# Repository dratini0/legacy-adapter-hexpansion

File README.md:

# "Legacy" connector adapter

Adapts the tildagon to various other interfaces.

* Any of the various I2C over JST SH standards (Compatible with Adafruit Stemma QT/Sparkfun Qwiic)
* [Shitty Add-On](https://hackaday.io/project/52950-shitty-add-ons/log/159806-introducing-the-shitty-add-on-v169bis-standard/)
* The expansion connector from TiDAL (hence the name)

## Acknowledgements

Uses the [hexpansion template from EMF](https://github.com/emfcamp/badge-2024-hardware/tree/main/hexpansion).
The footprint for the TiDAL expansion connector is also (unsurprisingly) [borrowed from EMF](https://github.com/emfcamp/TiDAL-Hardware/blob/main/tilda6/tilda6.pretty/XUNPU_FPC-05F-8PH20.kicad_mod).

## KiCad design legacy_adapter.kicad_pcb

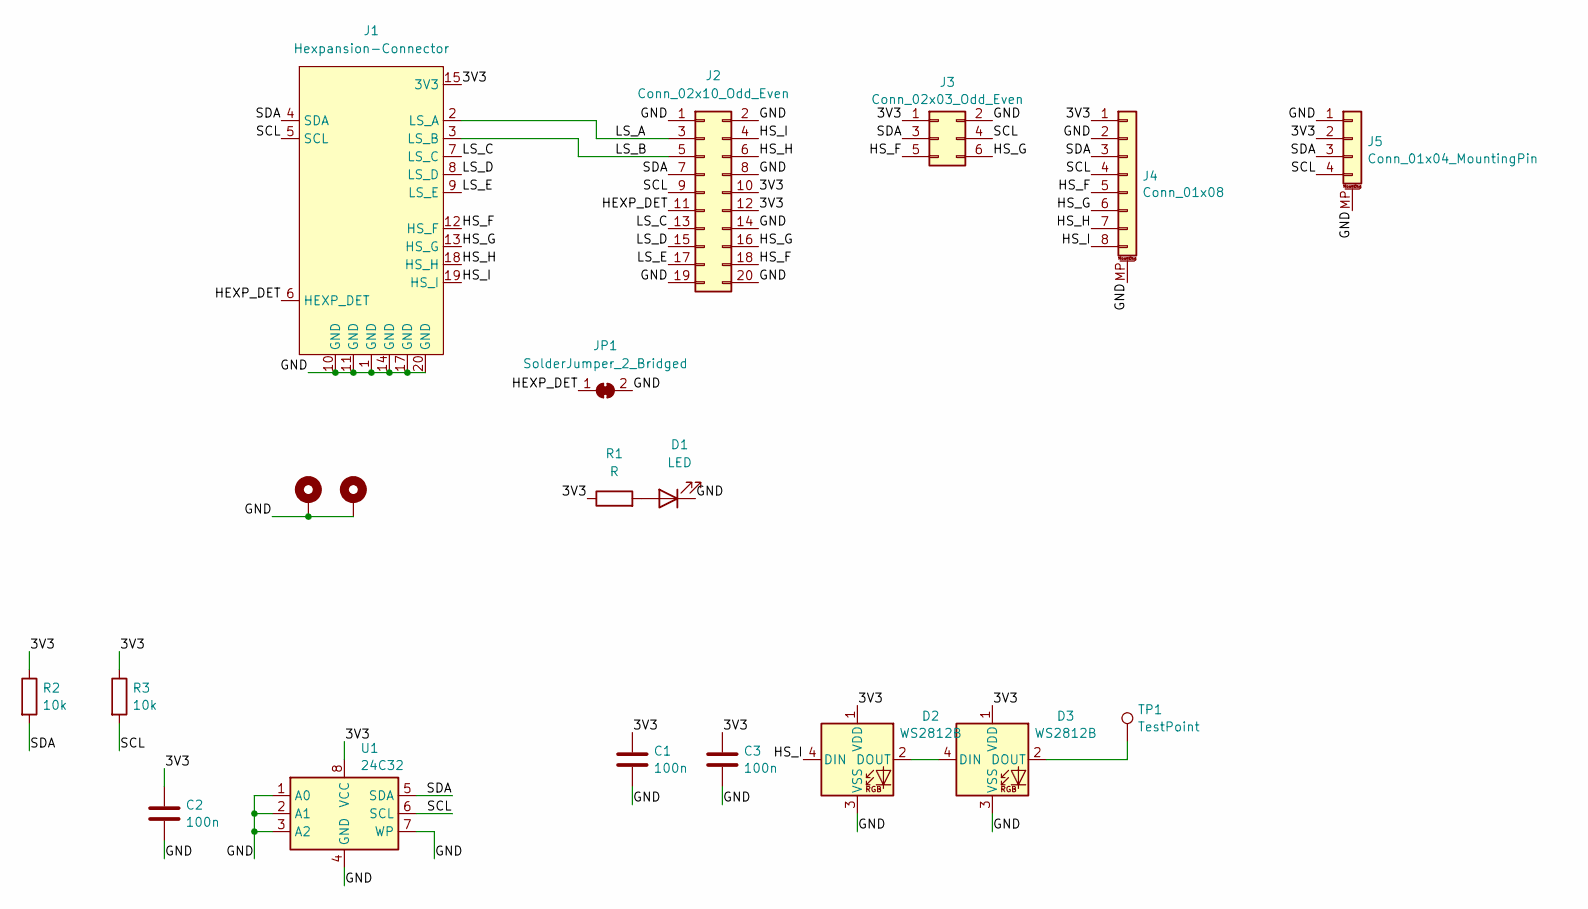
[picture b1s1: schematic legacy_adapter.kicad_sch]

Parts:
C1, C2, C3: 100n; C_0805_2012Metric_Pad1.18x1.45mm_HandSolder
D1: LED; LED_0805_2012Metric
D2, D3: WS2812B; LED_WS2812B_PLCC4_5.0x5.0mm_P3.2mm
H1, H2: MountingHole_Pad; MountingHole_2.2mm_M2_Pad_Via
J1: Hexpansion-Connector; hexpansion-edge-connector
J2: Conn_02x10_Odd_Even; PinHeader_2x10_P2.54mm_Vertical
J3: Conn_02x03_Odd_Even; PinSocket_2x03_P2.54mm_Vertical
J4: Conn_01x08; XUNPU_FPC-05F-8PH20
J5: Conn_01x04_MountingPin; JST_SH_SM04B-SRSS-TB_1x04-1MP_P1.00mm_Horizontal
JP1: SolderJumper_2_Bridged; SolderJumper-2_P1.3mm_Bridged_RoundedPad1.0x1.5mm
R1: R; R_0805_2012Metric_Pad1.20x1.40mm_HandSolder
R2, R3: 10k; R_0805_2012Metric_Pad1.20x1.40mm_HandSolder
TP1: TestPoint; TestPoint_THTPad_D2.0mm_Drill1.0mm
U1: 24C32; SOIC-8_3.9x4.9mm_P1.27mm

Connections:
/3V3: C1.1, C2.1, C3.1, D2.1 (VDD), D3.1 (VDD), J1.15 (3V3), J1.16 (3V3), J2.10, J2.12, J3.1, J4.1, J5.2, R1.1, R2.1, R3.1, U1.8 (VCC)
/GND: C1.2, C2.2, C3.2, D1.1 (K), D2.3 (VSS), D3.3 (VSS), H1.1, H2.1, J1.1 (GND), J1.10 (GND), J1.11 (GND), J1.14 (GND), J1.17 (GND), J1.20 (GND), J2.1, J2.2, J2.8, J2.14, J2.19, J2.20, J3.2, J4.2, J4.MP (MountPin), J5.1, J5.MP (MountPin), JP1.2 (B), U1.1 (A0), U1.2 (A1), U1.3 (A2), U1.4 (GND), U1.7 (WP)
/HEXP_DET: J1.6 (HEXP_DET), J2.11, JP1.1 (A)
/HS_F: J1.12 (HS_F), J2.18, J3.5, J4.5
/HS_G: J1.13 (HS_G), J2.16, J3.6, J4.6
/HS_H: J1.18 (HS_H), J2.6, J4.7
/HS_I: D2.4 (DIN), J1.19 (HS_I), J2.4, J4.8
/LS_A: J1.2 (LS_A), J2.3
/LS_B: J1.3 (LS_B), J2.5
/LS_C: J1.7 (LS_C), J2.13
/LS_D: J1.8 (LS_D), J2.15
/LS_E: J1.9 (LS_E), J2.17
/SCL: J1.5 (SCL), J2.9, J3.4, J4.4, J5.4, R3.2, U1.6 (SCL)
/SDA: J1.4 (SDA), J2.7, J3.3, J4.3, J5.3, R2.2, U1.5 (SDA)
unnamed: D1.2 (A), R1.2
unnamed: D2.2 (DOUT), D3.4 (DIN)
unnamed: D3.2 (DOUT), TP1.1

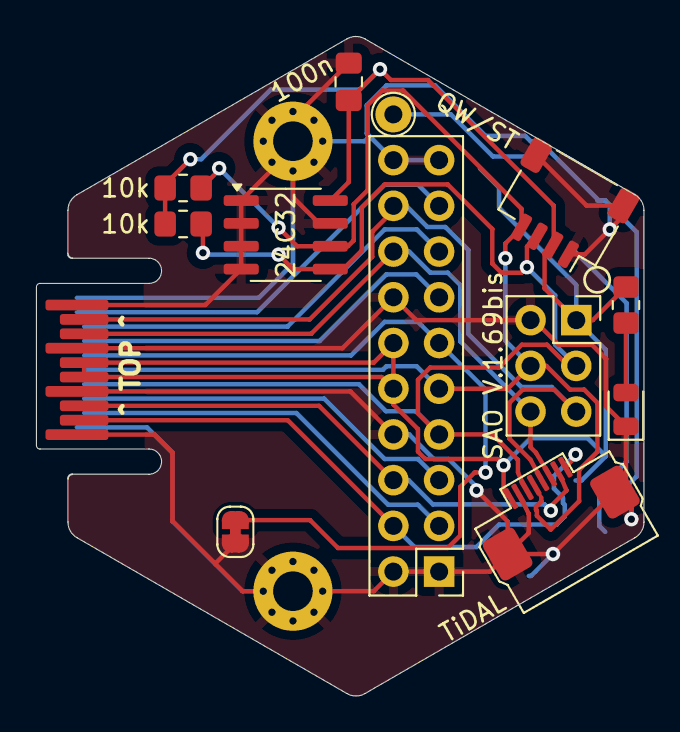
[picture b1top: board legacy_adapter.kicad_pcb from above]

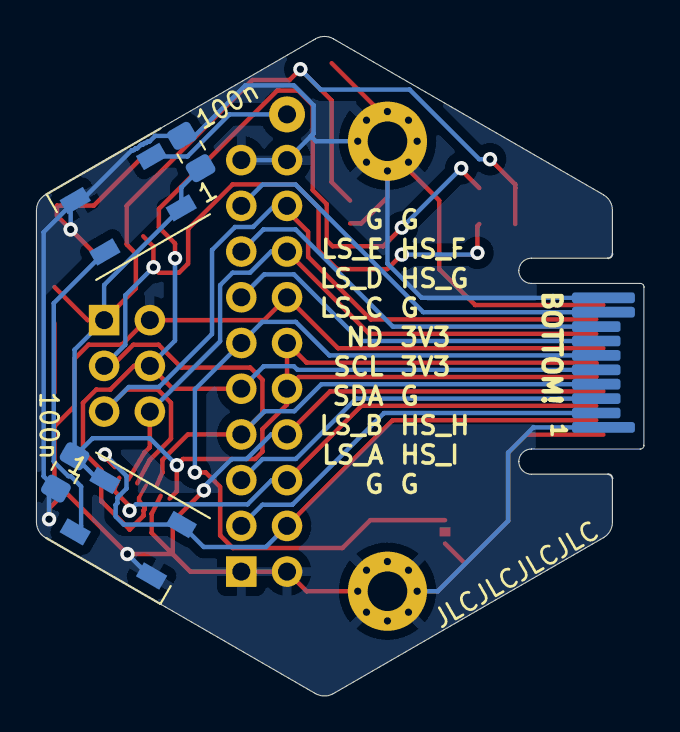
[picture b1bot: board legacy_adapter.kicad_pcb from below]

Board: 2 copper layers, 33.7 x 36.6 mm, 19 parts (4 on the bottom side), 17 nets.

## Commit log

2024-05-28 Initial check-in
